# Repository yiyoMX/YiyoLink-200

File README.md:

# YiyoLink-200
TI CC1111 BLE BRIDGE

What is it?
A SMART Bluetooth 4.2 LE module based on nrf51822, it allows for a Texas Instruments CC-1111 USB DNGL to communicate to any BLE compatible device. It can act as a transparent UART bridge.

How does it works?
Simply plug in the CC-1111 with the header pins. You could also plug jumper wires to connect any device via UART. Can flash firmware to BLE module via OTA, using an Iphone.

Features?
- TI-CC1111 header pins compatible socket.
- 2-pin JST-PH battery connector.
- Micro USB Lithium-ion battery charger.
- Charging led indicator (goes off when fully charged).
- Smart BLE 4.2 BMD-200.
- BLE connected indicator.
- On/Off switch.
- Exposed pwr pads to solder external charging source. (wireless charging? - not tested)
- Small footprint.

Limitations.
-Due to the version of BLE, only 20 bytes are allowed per write.

How does it looks?

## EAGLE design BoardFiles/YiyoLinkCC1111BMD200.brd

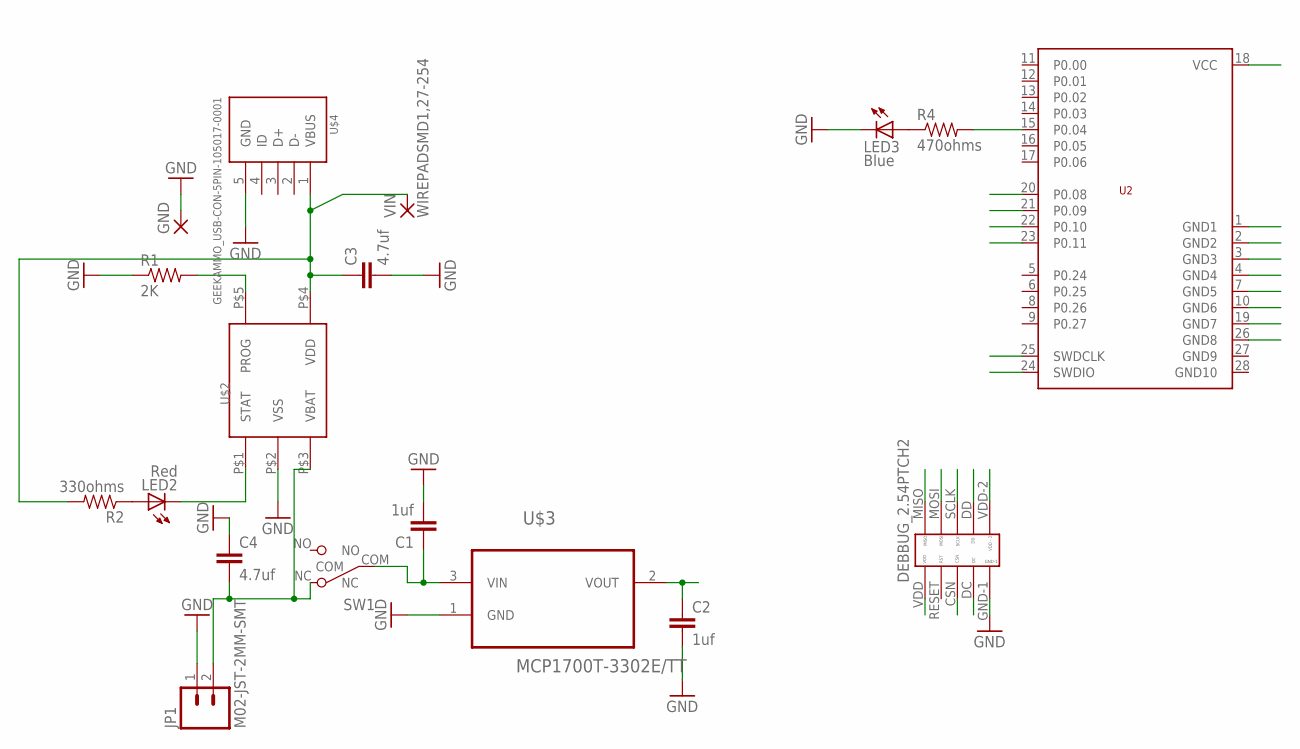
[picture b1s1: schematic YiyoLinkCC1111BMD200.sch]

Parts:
C1, C2: 1uf; 0805-CAP
C3, C4: 4.7uf; 0805
DEBBUG_2.54PTCH2: YIYOSLIBRARY_5X2_HEADER; YIYOSLIBRARY_5X2_FEMALE_HEADER
GND: WIREPADSMD1,27-254; SMD1,27-2,54
JP1: M02-JST-2MM-SMT; JST-2-SMD
LED2: Red; SML0805
LED3: Blue; SML0805
R1: 2K; 0805
R2: 330ohms; 0805
R4: 470ohms; 0805
SW1: SW_SLIDE; SLIDE_SWITCH_SMD
U2: BMD-200
U$2: MCP73831; 5PIN_SOT23
U$3: MCP1700T-3302E/TT; SOT95P237X112-3N
U$4: GEEKAMMO_USB-CON-5PIN-105017-0001; GEEKAMMO_USB-MICRO-MOLEX-105017-0001
VIN: WIREPADSMD1,27-254; SMD1,27-2,54

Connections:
CSN: DEBBUG_2.54PTCH2.CSN, U2.20 (P0.08)
DC: DEBBUG_2.54PTCH2.DC, U2.25 (SWDCLK)
DD: DEBBUG_2.54PTCH2.DD, U2.24 (SWDIO)
GND: C1.2, C2.2, C3.2, C4.1, DEBBUG_2.54PTCH2.GND-1, GND.1, JP1.1 (2), LED3.C, R1.1, U2.1 (GND1), U2.2 (GND2), U2.3 (GND3), U2.4 (GND4), U2.7 (GND5), U2.10 (GND6), U2.19 (GND7), U2.26 (GND8), U$2.P$2 (VSS), U$3.1 (GND), U$4.5 (GND)
MISO: DEBBUG_2.54PTCH2.MISO, U2.22 (P0.10)
MOSI: DEBBUG_2.54PTCH2.MOSI, U2.21 (P0.09)
unnamed: LED3.A, R4.1
unnamed: R4.2, U2.15 (P0.04)
unnamed: LED2.A, R2.1
unnamed: C3.1, R2.2, U$2.P$4 (VDD), U$4.1 (VBUS), VIN.1
unnamed: R1.2, U$2.P$5 (PROG)
unnamed: C4.2, JP1.2 (1), SW1.NC, U$2.P$3 (VBAT)
unnamed: C1.1, SW1.COM, U$3.3 (VIN)
unnamed: LED2.C, U$2.P$1 (STAT)
SCLK: DEBBUG_2.54PTCH2.SCLK, U2.23 (P0.11)
VDDO: C2.1, DEBBUG_2.54PTCH2.VDD, DEBBUG_2.54PTCH2.VDD-2, U2.18 (VCC), U$3.2 (VOUT)

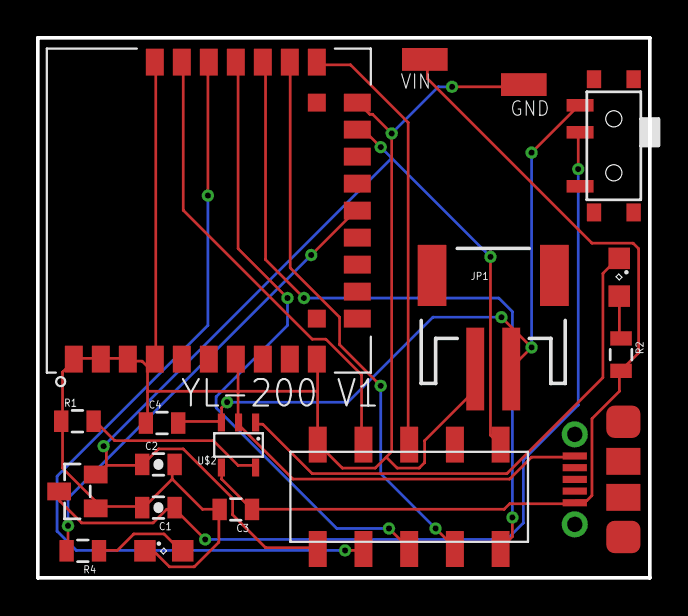
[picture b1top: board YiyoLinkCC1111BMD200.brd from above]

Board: 2 copper layers, 34.0 x 30.0 mm, 18 parts (0 on the bottom side), 16 nets.

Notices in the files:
parts and their libraries:
SparkFun-Capacitors: Licensing: Creative Commons ShareAlike 4.0 International - https://creativecommons.org/licenses/by-sa/4.0
